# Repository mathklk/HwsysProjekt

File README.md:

# Hardwarenahe Systementwicklung

Projekt, das im Rahmen des Moduls "Hardwarenahe Systementwicklung" an der Universität Oldenburg entstanden ist.

## Software

Die Software ist in C geschrieben und wurde mit PlatformIO und dem [Small Devices C Compiler](https://sourceforge.net/projects/sdcc/files/) entwickelt.
Zum Flashen über den USB-Programmer wird [avrdude](https://www.nongnu.org/avrdude/) benötigt.
Unter `software/src/` liegen verschiedene Testprogramme für eine schrittweise Inbetriebnahme, sowie das finale Programm FlappyBird.

## Hardware

Das PCB wurde mit [EAGLE Free](https://www.autodesk.de/products/eagle/free-download) designt.
Unter `hardware/` liegen Schematic, Layout und die verwendete Library.

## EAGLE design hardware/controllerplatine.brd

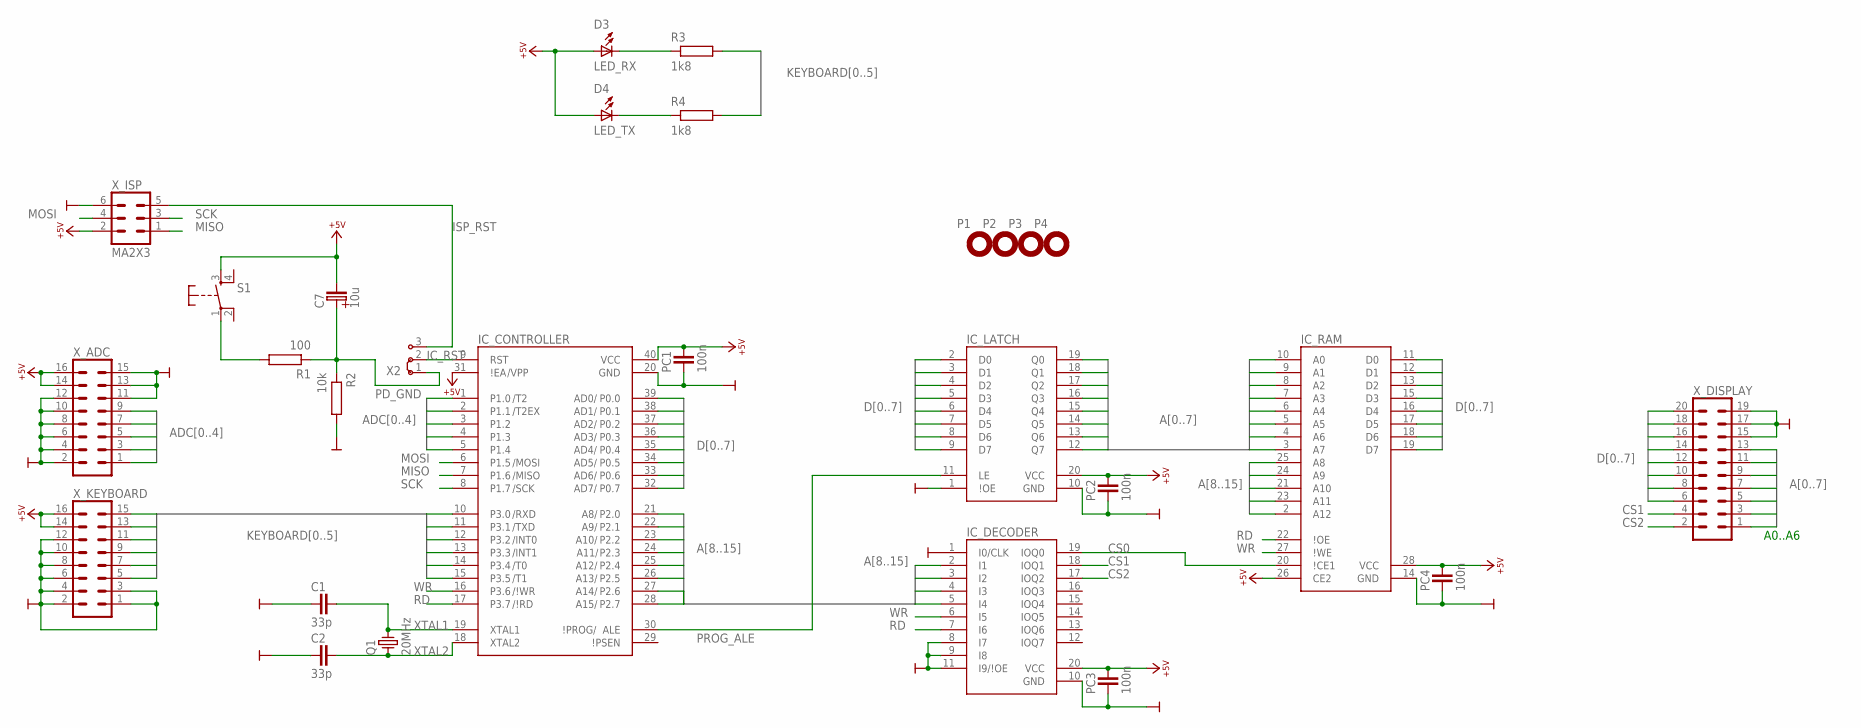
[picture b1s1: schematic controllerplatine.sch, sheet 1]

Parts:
C1, C2: 33p; C-2,5
C7: 10u; ELKO-2,5
D3: LED_RX; LED3-2,5
D4: LED_TX; LED3-2,5
IC_CONTROLLER: AT89S52; DIL40
IC_DECODER: 16V8; DIL20
IC_LATCH: 74573; DIL20
IC_RAM: 6264; DIL28
P1, P2, P3, P4: MPAD-3,0
PC1, PC2, PC3, PC4: 100n; C-2,5
Q1: 20MHz; HC49U
R1: 100; R-10
R2: 10k; R-10
R3, R4: 1k8; R-10_LANG
S1: KEY-3301; T3301
X2: J1X3
X_ADC: MA8X2
X_DISPLAY: MA10X2
X_ISP: MA2X3; MA3X2
X_KEYBOARD: MA8X2

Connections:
+5V: C7.-, D3.A, D4.A, IC_CONTROLLER.31 (\!EA), IC_CONTROLLER.40 (VCC), IC_DECODER.20 (VCC), IC_LATCH.20 (VCC), IC_RAM.26 (CE2), IC_RAM.28 (VCC), PC1.2, PC2.2, PC3.2, PC4.2, S1.3 (S), X_ADC.14, X_ADC.16, X_ISP.2, X_KEYBOARD.14, X_KEYBOARD.16; also elsewhere on the board
A0: IC_LATCH.19 (Q0), IC_RAM.10 (A0), X_DISPLAY.13
A1: IC_LATCH.18 (Q1), IC_RAM.9 (A1), X_DISPLAY.11
A2: IC_LATCH.17 (Q2), IC_RAM.8 (A2), X_DISPLAY.9
A3: IC_LATCH.16 (Q3), IC_RAM.7 (A3), X_DISPLAY.7
A4: IC_LATCH.15 (Q4), IC_RAM.6 (A4), X_DISPLAY.5
A5: IC_LATCH.14 (Q5), IC_RAM.5 (A5), X_DISPLAY.3
A6: IC_LATCH.13 (Q6), IC_RAM.4 (A6), X_DISPLAY.1
A7: IC_LATCH.12 (Q7), IC_RAM.3 (A7)
A8: IC_CONTROLLER.21 (P2.0), IC_RAM.25 (A8)
A9: IC_CONTROLLER.22 (P2.1), IC_RAM.24 (A9)
A10: IC_CONTROLLER.23 (P2.2), IC_RAM.21 (A10)
A11: IC_CONTROLLER.24 (P2.3), IC_RAM.23 (A11)
A12: IC_CONTROLLER.25 (P2.4), IC_DECODER.5 (I4), IC_RAM.2 (A12)
A13: IC_CONTROLLER.26 (P2.5), IC_DECODER.4 (I3)
A14: IC_CONTROLLER.27 (P2.6), IC_DECODER.3 (I2)
A15: IC_CONTROLLER.28 (P2.7), IC_DECODER.2 (I1)
ADC0: IC_CONTROLLER.1 (P1.0), X_ADC.9
ADC1: IC_CONTROLLER.2 (P1.1), X_ADC.7
ADC2: IC_CONTROLLER.3 (P1.2), X_ADC.5
ADC3: IC_CONTROLLER.4 (P1.3), X_ADC.3
ADC4: IC_CONTROLLER.5 (P1.4), X_ADC.1
CS0: IC_DECODER.19 (IOQ0), IC_RAM.20 (\!CE1)
CS1: IC_DECODER.18 (IOQ1), X_DISPLAY.4
CS2: IC_DECODER.17 (IOQ2), X_DISPLAY.2
D0: IC_CONTROLLER.39 (P0.0), IC_LATCH.2 (D0), IC_RAM.11 (D0), X_DISPLAY.20
D1: IC_CONTROLLER.38 (P0.1), IC_LATCH.3 (D1), IC_RAM.12 (D1), X_DISPLAY.18
D2: IC_CONTROLLER.37 (P0.2), IC_LATCH.4 (D2), IC_RAM.13 (D2), X_DISPLAY.16
D3: IC_CONTROLLER.36 (P0.3), IC_LATCH.5 (D3), IC_RAM.15 (D3), X_DISPLAY.14
D4: IC_CONTROLLER.35 (P0.4), IC_LATCH.6 (D4), IC_RAM.16 (D4), X_DISPLAY.12
D5: IC_CONTROLLER.34 (P0.5), IC_LATCH.7 (D5), IC_RAM.17 (D5), X_DISPLAY.10
D6: IC_CONTROLLER.33 (P0.6), IC_LATCH.8 (D6), IC_RAM.18 (D6), X_DISPLAY.8
D7: IC_CONTROLLER.32 (P0.7), IC_LATCH.9 (D7), IC_RAM.19 (D7), X_DISPLAY.6
GND: C1.1, C2.1, IC_CONTROLLER.20 (GND), IC_DECODER.1 (I0/CLK), IC_DECODER.8 (I7), IC_DECODER.9 (I8), IC_DECODER.10 (GND), IC_DECODER.11 (I9/\!OE), IC_LATCH.1 (\!OE), IC_LATCH.10 (GND), IC_RAM.14 (GND), PC1.1, PC2.1, PC3.1, PC4.1, R2.2, X_ADC.2, X_ADC.4, X_ADC.6, X_ADC.8, X_ADC.10, X_ADC.11, X_ADC.12, X_ADC.13, X_ADC.15, X_DISPLAY.15, X_DISPLAY.17, X_DISPLAY.19, X_ISP.6, X_KEYBOARD.1, X_KEYBOARD.2, X_KEYBOARD.3, X_KEYBOARD.4, X_KEYBOARD.6, X_KEYBOARD.8, X_KEYBOARD.10, X_KEYBOARD.12; also elsewhere on the board
IC_RST: IC_CONTROLLER.9 (RST), X2.2
ISP_RST: X2.3, X_ISP.5
KEYBOARD0: IC_CONTROLLER.10 (P3.0), R3.2, X_KEYBOARD.15
KEYBOARD1: IC_CONTROLLER.11 (P3.1), R4.2, X_KEYBOARD.13
KEYBOARD2: IC_CONTROLLER.12 (P3.2), X_KEYBOARD.11
KEYBOARD3: IC_CONTROLLER.13 (P3.3), X_KEYBOARD.9
KEYBOARD4: IC_CONTROLLER.14 (P3.4), X_KEYBOARD.7
KEYBOARD5: IC_CONTROLLER.15 (P3.5), X_KEYBOARD.5
MISO: IC_CONTROLLER.7 (P1.6), X_ISP.1
MOSI: IC_CONTROLLER.6 (P1.5), X_ISP.4
unnamed: R1.2, S1.1
unnamed: D3.C, R3.1
unnamed: D4.C, R4.1
PD_GND: C7.+, R1.1, R2.1, X2.1
PROG_ALE: IC_CONTROLLER.30 (ALE), IC_LATCH.11 (LE)
RD: IC_CONTROLLER.17 (P3.7), IC_DECODER.7 (I6), IC_RAM.22 (\!OE)
SCK: IC_CONTROLLER.8 (P1.7), X_ISP.3
WR: IC_CONTROLLER.16 (P3.6), IC_DECODER.6 (I5), IC_RAM.27 (\!WE)
XTAL1: C1.2, IC_CONTROLLER.19 (XTAL1), Q1.2
XTAL2: C2.2, IC_CONTROLLER.18 (XTAL2), Q1.1

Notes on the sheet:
A0..A6

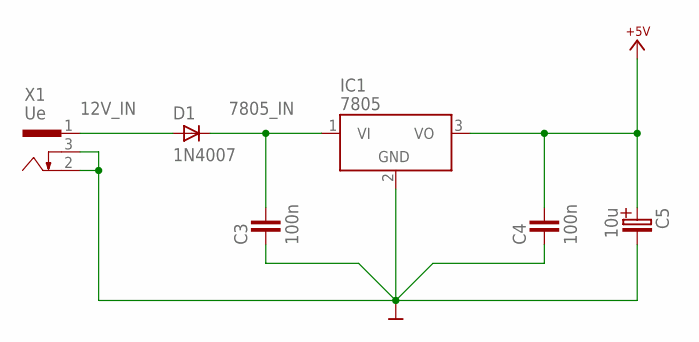
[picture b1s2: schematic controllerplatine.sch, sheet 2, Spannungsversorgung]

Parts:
C3, C4: 100n; C-2,5
C5: 10u; ELKO-2,5
D1: 1N4007; DO41-10
IC1: 7805; TO220V
X1: Ue; HEBW21

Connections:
12V_IN: D1.A, X1.1
7805_IN: C3.2, D1.C, IC1.1 (VI)
+5V: C4.2, C5.+, IC1.3 (VO); also elsewhere on the board
GND: C3.1, C4.1, C5.-, IC1.2 (GND), X1.2, X1.3; also elsewhere on the board

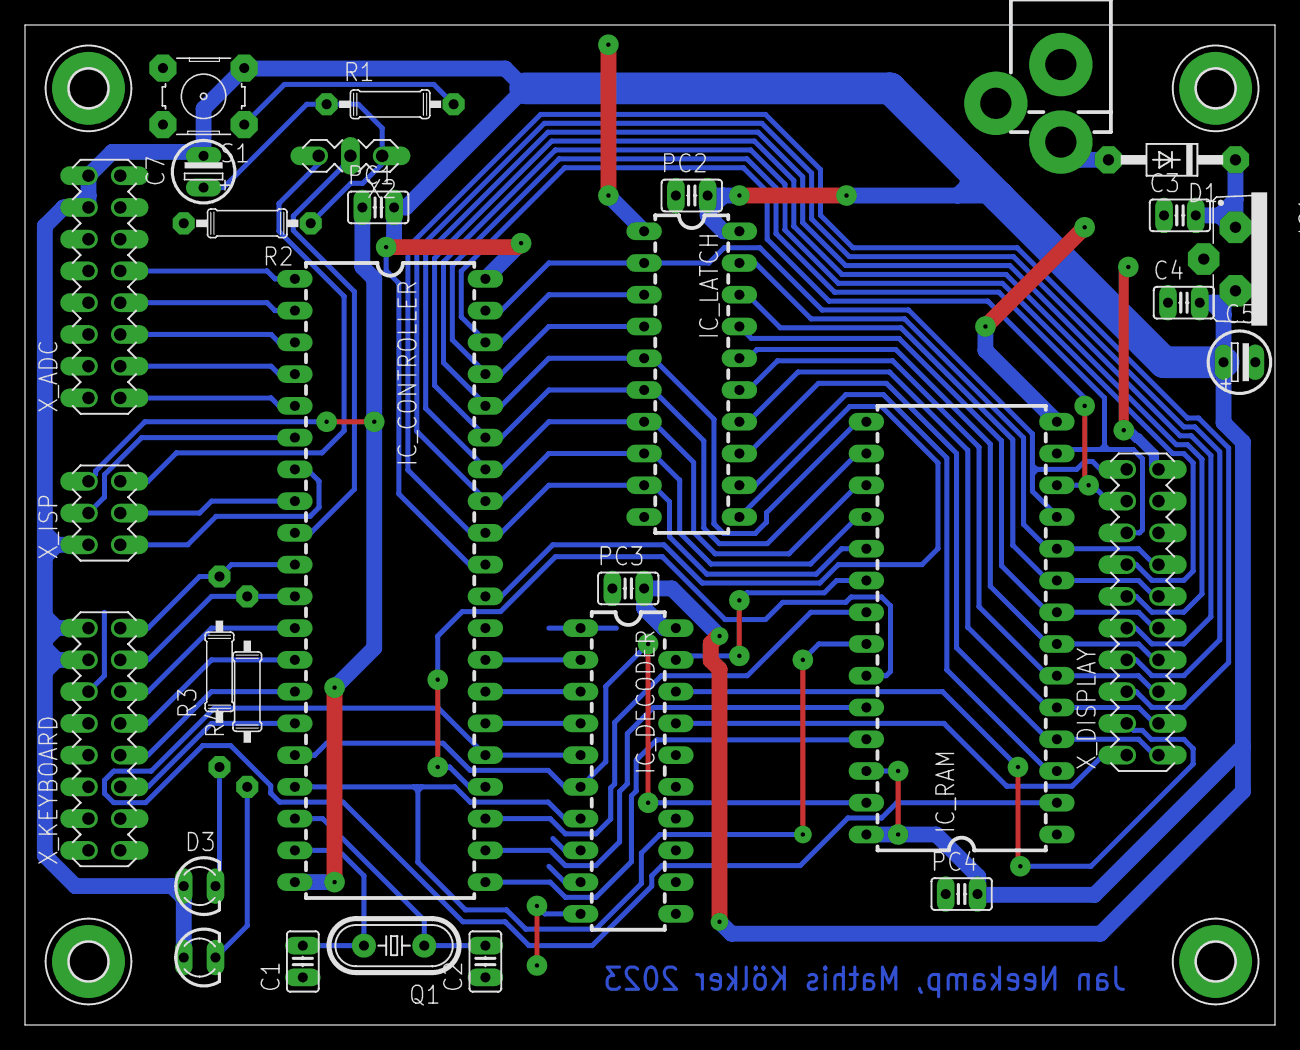
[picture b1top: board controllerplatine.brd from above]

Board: 2 copper layers, 100.0 x 80.0 mm, 34 parts (0 on the bottom side), 56 nets.
